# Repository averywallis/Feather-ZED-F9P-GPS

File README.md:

# Feather-ZED-F9P-GPS
 KiCad files for a ZED-F9P GPS Featherwing

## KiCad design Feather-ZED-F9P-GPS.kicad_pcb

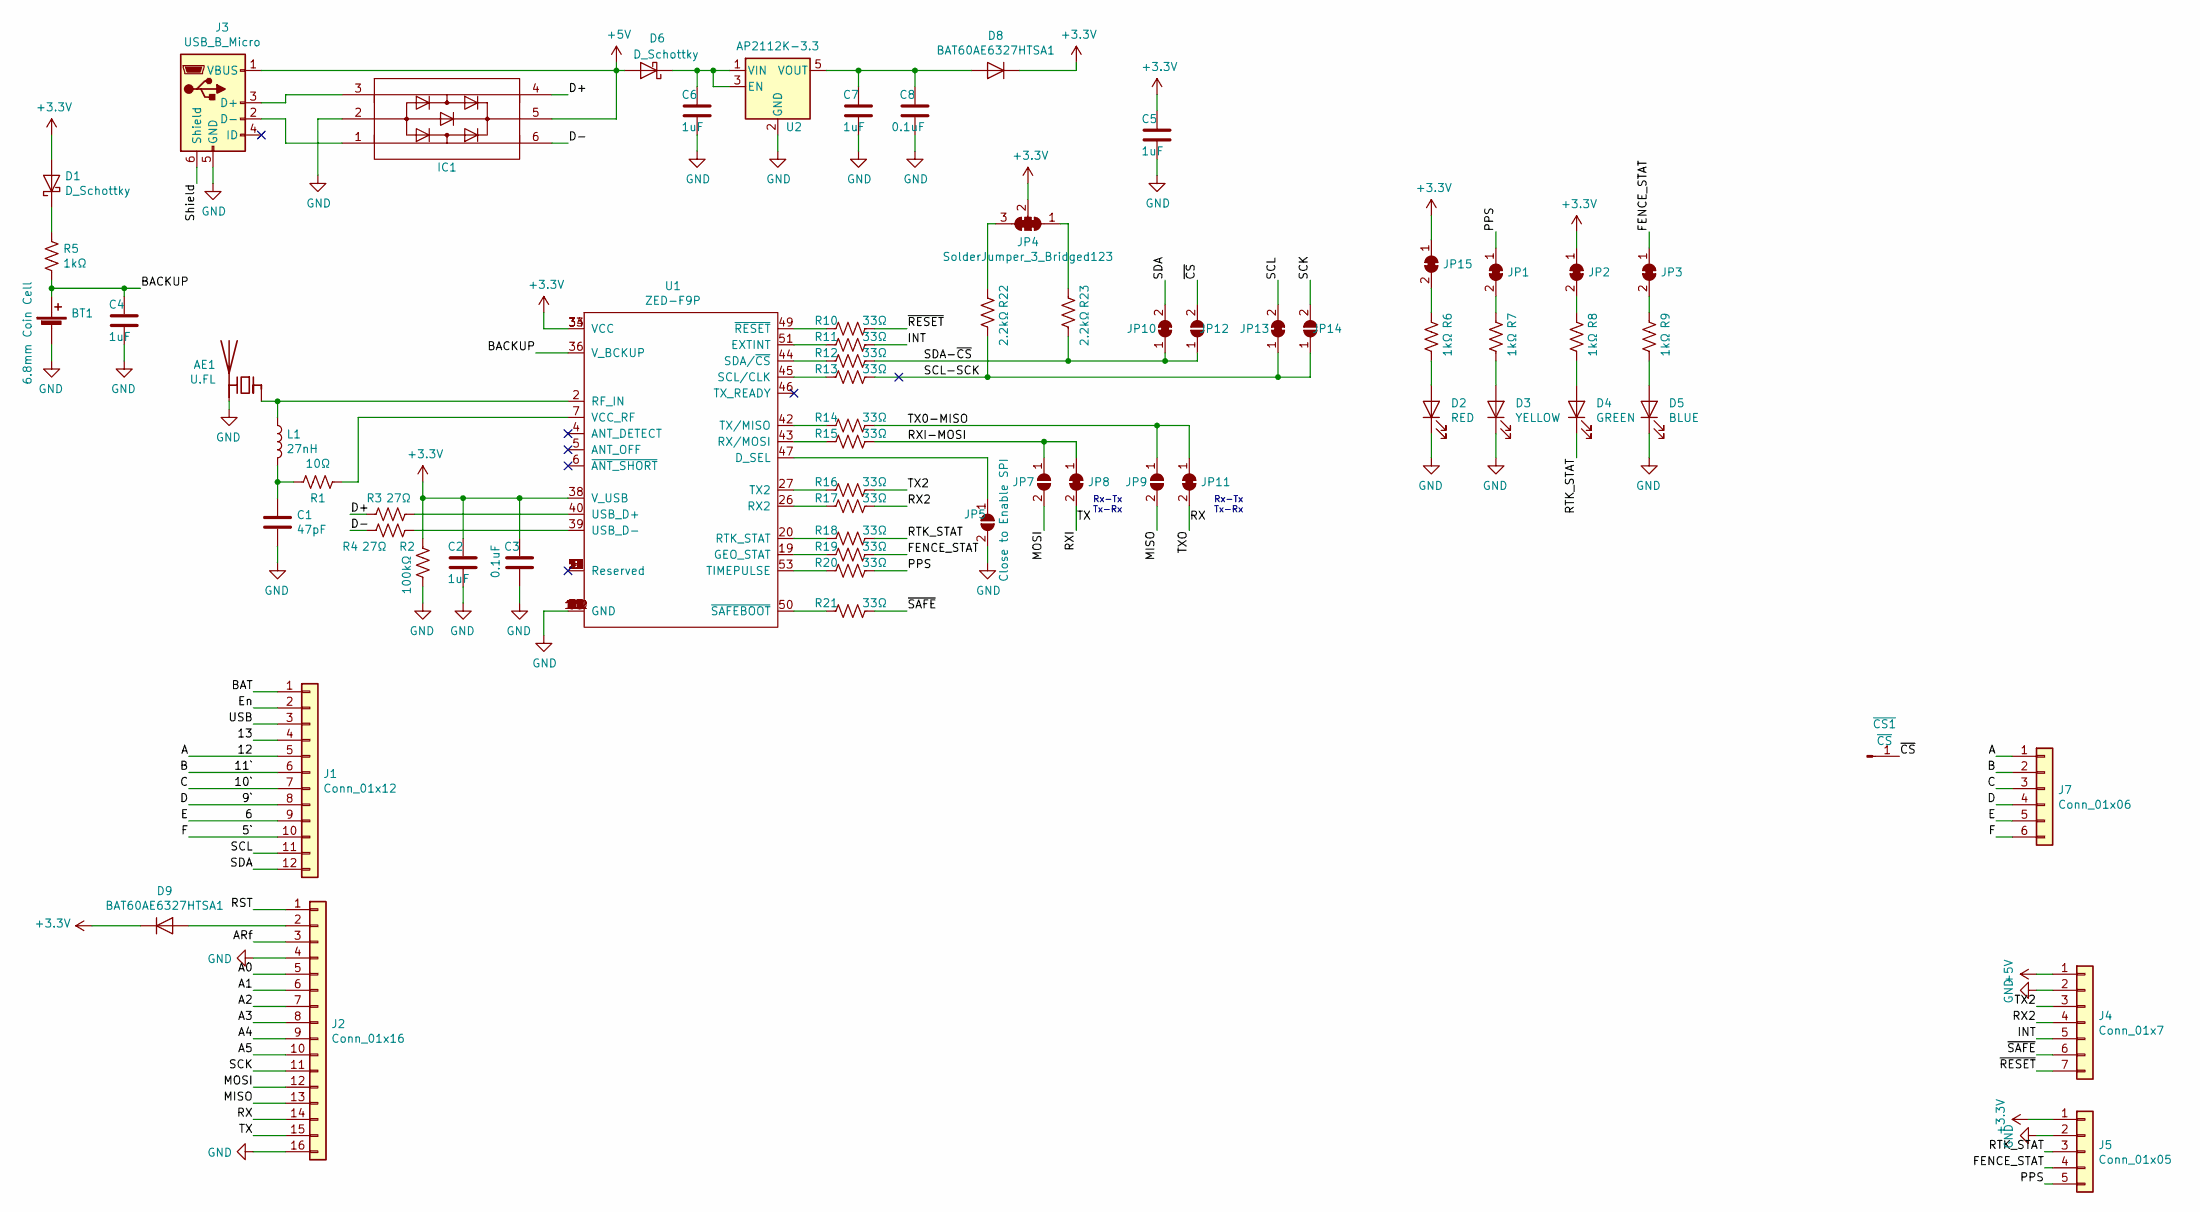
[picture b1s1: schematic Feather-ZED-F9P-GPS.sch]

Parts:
AE1: U.FL; U.FL_Hirose_U.FL-R-SMT-1_Vertical; MPN U.FL-R-SMT-1(01)
BT1: 6.8mm Coin Cell; BatteryHolder_Seiko_MS621F; MPN MS621FE-FL11E
C1: 47pF; C_0603_1608Metric; MPN CL21C470JBANNNC
C2, C4, C5, C6, C7: 1uF; C_0603_1608Metric; MPN CL21B105KOFNNNE
C3, C8: 0.1uF; C_0603_1608Metric; MPN CL21B104KACNNNC
D1, D6: D_Schottky; D_SOD-323F; MPN PMEG4005EJF
D2: RED; D_0805_2012Metric; MPN LTST-S220KRKT
D3: YELLOW; D_0805_2012Metric; MPN LTST-C171KSKT
D4: GREEN; D_0805_2012Metric; MPN LTST-S220KGKT
D5: BLUE; D_0805_2012Metric; MPN LTST-C171TBKT
D8, D9: BAT60AE6327HTSA1; SOD2513X110N; MPN BAT60AE6327HTSA1
IC1: 74LVC1G27GM115; MPN PRTR5V0U2F,115; Mouser Part Number 771-PRTR5V0U2F-T/R
J1: Conn_01x12; PinHeader_1x12_P2.54mm_Vertical
J2: Conn_01x16; PinHeader_1x16_P2.54mm_Vertical
J3: USB_B_Micro; USB_Micro-B_Molex_47346-0001; MPN 47346-0001
J4: Conn_01x7; PinSocket_1x07_P2.54mm_Vertical
J5: Conn_01x05; PinSocket_1x05_P2.54mm_Vertical
J7: Conn_01x06; PinSocket_1x06_P2.54mm_Vertical
JP1, JP2, JP3, JP8, JP10, JP11, JP13, JP15: SolderJumper-2_P1.3mm_Bridged_RoundedPad1.0x1.5mm
JP4: SolderJumper_3_Bridged123; SMT-JUMPER_3_2-NC_TRACE_SILK
JP5: Close to Enable SPI; SolderJumper-2_P1.3mm_Open_RoundedPad1.0x1.5mm
JP7, JP9, JP12, JP14: SolderJumper-2_P1.3mm_Open_RoundedPad1.0x1.5mm
L1: 27nH; L_0603_1608Metric; MPN CE201210-27NJ
R1: 10Ω; R_0603_1608Metric; MPN RMCF0805FT10R0
R2: 100kΩ; R_0603_1608Metric; MPN RMCF0805JT100K
R3, R4: 27Ω; R_0603_1608Metric; MPN RMCF0805JT27R0
R5, R6, R7, R8, R9: 1kΩ; R_0603_1608Metric; MPN ERJ-P06J102V
R10, R11, R12, R13, R14, R15, R16, R17, R18, R19, R20, R21: 33Ω; R_0603_1608Metric; MPN RMCF0805JT33R0
R22, R23: 2.2kΩ; R_0603_1608Metric; MPN RMCF0805FT2K20
U1: ZED-F9P; ublox_ZED-F9P; MPN ZED-F9P-00B-02
U2: AP2112K-3.3; SOT-23-5; MPN AP2112K-3.3
~CS1: ~CS; Pin_D1.0mm_L10.0mm

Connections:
+3V3: C2.1, C3.1, C5.1, D1.2 (A), D8.1 (K), D9.1 (K), J5.1, JP2.1 (A), JP4.2 (C), JP15.1 (A), R2.1, U1.33 (VCC), U1.34 (VCC), U1.38 (V_USB)
+5V: D6.2 (A), IC1.5, J3.1 (VBUS), J4.1
/5`: J1.10, J7.6
/6: J1.9, J7.5
/9`: J1.8, J7.4
/10`: J1.7, J7.3
/11`: J1.6, J7.2
/12: J1.5, J7.1
/13: J1.4
/A0: J2.5
/A1: J2.6
/A2: J2.7
/A3: J2.8
/A4: J2.9
/A5: J2.10
/ARf: J2.3
/BACKUP: BT1.1 (+), C4.1, R5.2, U1.36 (V_BCKUP)
/BAT: J1.1
/D+: IC1.4, R3.2
/D-: IC1.6, R4.2
/En: J1.2
/FENCE_STAT: J5.4, JP3.1 (A), R19.1
/INT: J4.5, R11.1
/MISO: J2.13, JP9.2 (B)
/MOSI: J2.12, JP7.2 (B)
/PPS: J5.5, JP1.1 (A), R20.1
/RST: J2.1
/RTK_STAT: D4.1 (K), J5.3, R18.1
/RX: J2.14, JP11.2 (B)
/RX2: J4.4, R17.1
/RXI: J2.15, JP8.2 (B)
/RXI-MOSI: JP7.1 (A), JP8.1 (A), R15.1
/SCK: J2.11, JP14.2 (B)
/SCL: J1.11, JP13.2 (B)
/SCL-SCK: JP13.1 (A), JP14.1 (A), R13.1, R22.1
/SDA: J1.12, JP10.2 (B)
/SDA-~CS: JP10.1 (A), JP12.1 (A), R12.1, R23.1
/Shield: J3.6 (Shield)
/TX0-MISO: JP9.1 (A), JP11.1 (A), R14.1
/TX2: J4.3, R16.1
/USB: J1.3
/~CS: JP12.2 (B), ~CS1.1
/~RESET: J4.7, R10.1
/~SAFE: J4.6, R21.1
GND: AE1.2 (PCB_Trace), BT1.2 (-), C1.1, C2.2, C3.2, C4.2, C5.2, C6.2, C7.2, C8.2, D2.1 (K), D3.1 (K), D5.1 (K), IC1.2, J2.4, J2.16, J3.5 (GND), J4.2, J5.2, JP5.2 (B), R2.2, U1.1 (GND), U1.3 (GND), U1.12 (GND), U1.14 (GND), U1.32 (GND), U1.37 (GND), U1.41 (GND), U1.48 (GND), U1.55 (GND), U1.56 (GND), U1.57 (GND), U1.58 (GND), U1.59 (GND), U1.60 (GND), U1.61 (GND), U1.62 (GND), U1.63 (GND), U1.64 (GND), U1.65 (GND), U1.66 (GND), U1.67 (GND), U1.68 (GND), U1.69 (GND), U1.70 (GND), U1.71 (GND), U1.72 (GND), U1.73 (GND), U1.74 (GND), U1.75 (GND), U1.76 (GND), U1.77 (GND), U1.78 (GND), U1.79 (GND), U1.80 (GND), U1.81 (GND), U1.82 (GND), U1.83 (GND), U1.84 (GND), U1.85 (GND), U1.86 (GND), U1.87 (GND), U1.88 (GND), U1.89 (GND), U1.90 (GND), U1.91 (GND), U1.92 (GND), U1.93 (GND), U1.94 (GND), U1.95 (GND), U1.96 (GND), U1.97 (GND), U1.98 (GND), U1.99 (GND), U1.100 (GND), U1.101 (GND), U1.102 (GND), U2.2 (GND); also elsewhere on the board
unnamed 45: AE1.1 (FEED), L1.1, U1.2 (RF_IN); also elsewhere on the board
unnamed: C1.2, L1.2, R1.2
unnamed: C6.1, D6.1 (K), U2.1 (VIN), U2.3 (EN)
unnamed: C7.1, C8.1, D8.2 (A), U2.5 (VOUT)
unnamed: D1.1 (K), R5.1
unnamed: D2.2 (A), R6.1
unnamed: D3.2 (A), R7.1
unnamed: D4.2 (A), R8.1
unnamed: D5.2 (A), R9.1
unnamed: D9.2 (A), J2.2
unnamed: IC1.1, J3.2 (D-)
unnamed: IC1.3, J3.3 (D+)
unnamed: JP1.2 (B), R7.2
unnamed: JP2.2 (B), R8.2
unnamed: JP3.2 (B), R9.2
unnamed: JP4.1 (A), R23.2
unnamed: JP4.3 (B), R22.2
unnamed: JP5.1 (A), U1.47 (D_SEL)
unnamed: JP15.2 (B), R6.2
unnamed: R1.1, U1.7 (VCC_RF)
unnamed: R3.1, U1.40 (USB_D+)
unnamed: R4.1, U1.39 (USB_D-)
unnamed: R10.2, U1.49 (~RESET)
unnamed: R11.2, U1.51 (EXTINT)
unnamed: R12.2, U1.44 (SDA/~CS)
unnamed: R13.2, U1.45 (SCL/CLK)
unnamed: R14.2, U1.42 (TX/MISO)
unnamed: R15.2, U1.43 (RX/MOSI)
unnamed: R16.2, U1.27 (TX2)
unnamed: R17.2, U1.26 (RX2)
unnamed: R18.2, U1.20 (RTK_STAT)
unnamed: R19.2, U1.19 (GEO_STAT)
unnamed: R20.2, U1.53 (TIMEPULSE)
unnamed: R21.2, U1.50 (~SAFEBOOT)
unnamed: U1.8 (Reserved), U1.9 (Reserved), U1.10 (Reserved), U1.11 (Reserved), U1.13 (Reserved), U1.15 (Reserved), U1.16 (Reserved), U1.17 (Reserved), U1.18 (Reserved), U1.21 (Reserved), U1.22 (Reserved), U1.23 (Reserved), U1.24 (Reserved), U1.25 (Reserved), U1.28 (Reserved), U1.29 (Reserved), U1.30 (Reserved), U1.31 (Reserved), U1.35 (Reserved), U1.52 (Reserved), U1.54 (Reserved)

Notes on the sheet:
Rx-Tx Tx-Rx

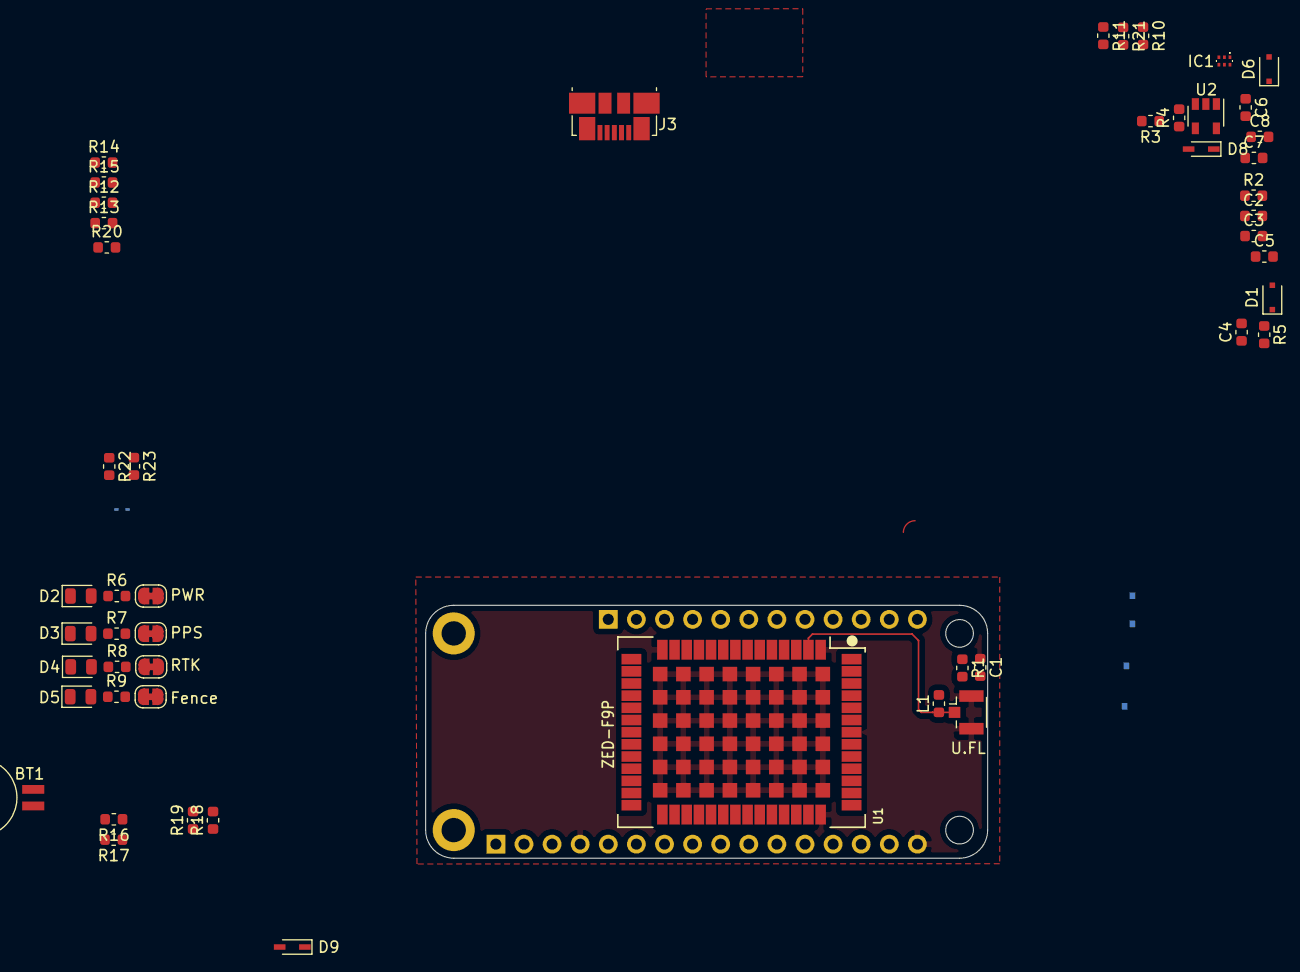
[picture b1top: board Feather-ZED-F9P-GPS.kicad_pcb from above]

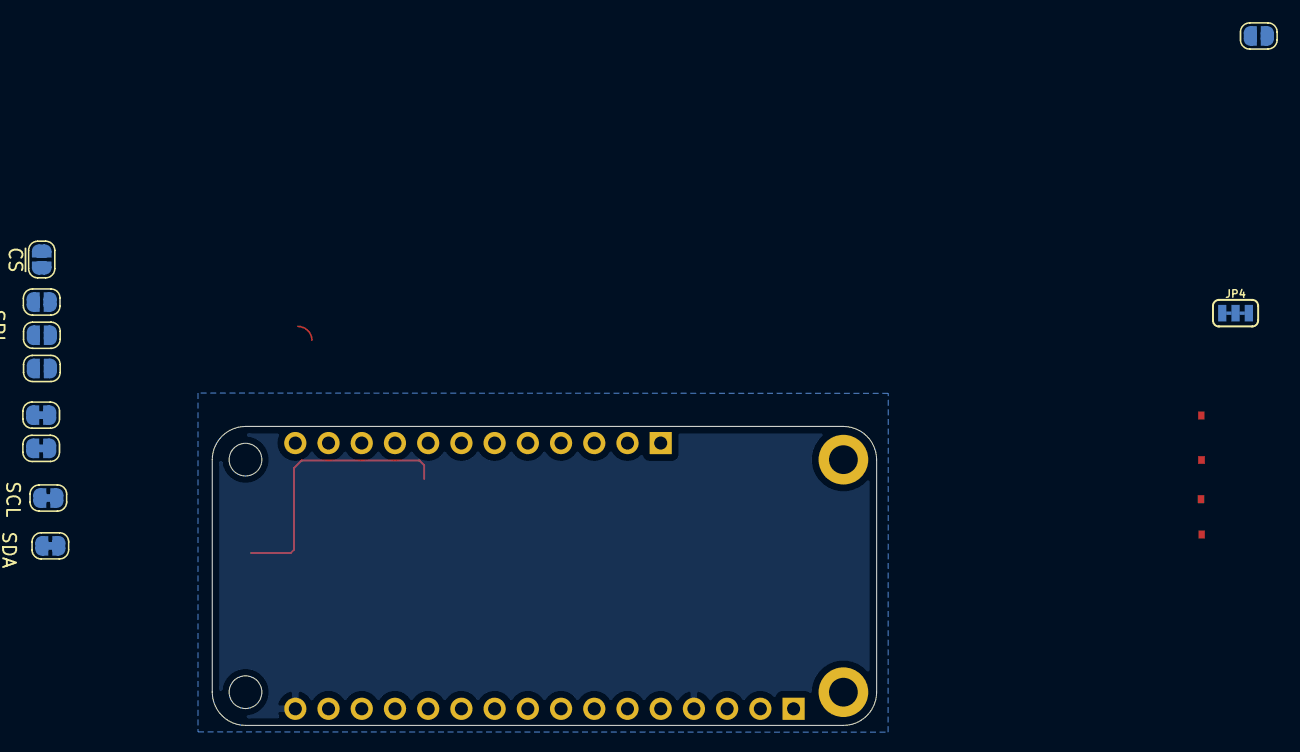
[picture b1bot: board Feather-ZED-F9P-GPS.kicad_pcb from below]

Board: 2 copper layers, 50.8 x 22.9 mm, 62 parts (10 on the bottom side), 55 nets.

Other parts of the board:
U.FL: U.FL; U.FL_Hirose_U.FL-R-SMT-1_Vertical

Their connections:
GND: U.FL.2; also elsewhere on the board
unnamed 45: U.FL.1; also elsewhere on the board

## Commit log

2020-01-24 Save Rev1 pcb
2020-10-23 Some edits?
    Some edits I made a while ago apparently? Don't remember the details but I'll push anways
2022-01-29 Create LICENSE
